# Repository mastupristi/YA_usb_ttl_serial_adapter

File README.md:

# USB-TTL Adapter with Auto Voltage Sensing

This is a simple open hardware project for a USB-to-TTL serial adapter based on the FTDI FT232RNL chip. The main feature of this adapter is its automatic voltage level detection, supporting TTL I/O levels from 1.8V to 5V without requiring manual jumper selection.

## Motivation

There are many USB-to-TTL adapters available on the market, such as:

- [AZDelivery FT232RL Adapter](https://www.amazon.it/AZDelivery-FT232RL-Adattatore-convertitore-Gratuito/dp/B01N9RZK6I)
- [DSD TECH SH-U09C2 Adapter](https://www.amazon.it/DSD-TECH-SH-U09C2-Adattatore-Programmazione/dp/B07TXVRQ7V/)

However, most of them require the user to manually set the voltage level using jumpers or switches. This can be inconvenient or even risky if the user forgets to set, or does not know exactly the correct voltage, potentially damaging the target device.

## Key Features

- Based on **FTDI FT232RNL** USB-serial bridge.
- Supports **1.8V to 5V TTL I/O levels**.
- **No jumpers or switches** required to select voltage.
- Uses **TI TXU0202** dual-channel voltage level translator for automatic level adaptation.
- Only **RX** and **TX** signals are used (no RTS/CTS or other control signals).
- Two mirrored TTL connectors with **inverted RX/TX** pinout for flexible wiring
- All schematic symbols and footprints have fields populated for **automated assembly on [JLCPCB](https://jlcpcb.com/)**

## Auto Voltage Detection

This adapter eliminates the need for manual voltage configuration. Thanks to the TXU0202 level shifter, the adapter automatically adapts to the voltage of the connected target device. This makes it safer and easier to use, especially when working with multiple devices operating at different logic levels.

## TTL Pinout

The board provides **two 1x4 pin headers** on the TTL side, with the same signals but **mirrored RX/TX orientation**. This simplifies usage with different target pinouts.

### Pinout (both connectors):

```
[ VCC_TTL | TX | RX | GND ]  ← Connector A
[ VCC_TTL | RX | TX | GND ]  ← Connector B (mirrored)
```

This layout helps avoid the common issue of crossed RX/TX lines between the adapter and the target device.

There are indications in the silkscreen to identify the VCC_TTL and GND pins.

## Manufacturing Support

This project includes files suitable for production with **[JLCPCB](https://jlcpcb.com/)**:

- [usb_uart_1V8_bom_top.csv](usb_uart_1V8_bom_top.csv) and [usb_uart_1V8_bom_bot.csv](usb_uart_1V8_bom_bot.csv): Bill of materials, with fields compatible with JLCPCB's parts selection tool (only **top** side populated)
- [usb_uart_1V8_cpl_top.csv](usb_uart_1V8_cpl_top.csv) and [usb_uart_1V8_cpl_bot.csv](usb_uart_1V8_cpl_bot.csv): Pick-and-place files (only **top** side contains components)
- All schematic symbols and footprints include **LCSC part numbers**, **JLC footprints** and assembly attributes

## Design Tools

This project was developed using **KiCad 9.0.1**.

## Repository Contents

- KiCad design files are on he root dir of the repo
- `usb_uart_1V8.pretty/`: local footprint library
- `gerber/`: Production-ready Gerber + drill files, packed in [grb_usb_uart_1V8.zip](gerber/grb_usb_uart_1V8.zip)

## Rendering

Here is a rendering of the board

## License

This project is licensed under the **CERN-OHL-S v2** open hardware license.
See [LICENSE.CERN-OHL-S_v2.txt](LICENSE) for more information.

## How to Contribute

Feel free to open issues or submit pull requests if you find bugs or want to suggest improvements.

## Acknowledgments

This project was inspired by the analysis in this blog post:
[https://www.electrothinks.com/2024/02/ft232rl-usb-to-serial-uart-module.html](https://www.electrothinks.com/2024/02/ft232rl-usb-to-serial-uart-module.html)

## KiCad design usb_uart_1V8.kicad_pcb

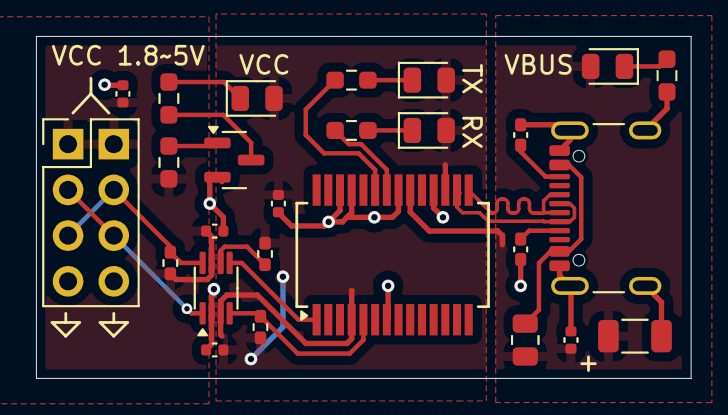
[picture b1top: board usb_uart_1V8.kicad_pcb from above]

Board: 2 copper layers, 36.4 x 19.0 mm, 26 parts (0 on the bottom side), 22 nets.

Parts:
C1, C3, C4, C5, C6: 100nF; C_0402_1005Metric
C2: 10uF; C_1206_3216Metric
D1, D2, D3, D4: NCD0805R1; LED_0805_2012Metric
FB1: GZ2012D601TF; R_0805_2012Metric
J1: USB_C_Receptacle_USB2.0_16P; USB_C_Receptacle_GCT_USB4105-xx-A_16P_TopMnt_Horizontal
J2: Conn_02x04_Odd_Even; PinHeader_2x04_P2.54mm_Vertical
Q1: MMBT3904; SOT-23
R1: 1k5; R_0603_1608Metric_Pad0.98x0.95mm_HandSolder
R2, R3: 270; R_0603_1608Metric_Pad0.98x0.95mm_HandSolder
R4, R5, R6: 10k; R_0402_1005Metric_Pad0.72x0.64mm_HandSolder
R7: 470; R_0603_1608Metric_Pad0.98x0.95mm_HandSolder
R8: 47k; R_0603_1608Metric_Pad0.98x0.95mm_HandSolder
R9, R10: 5k1; C_0402_1005Metric_Pad0.74x0.62mm_HandSolder
U1: FT232RNL; SSOP-28_5.3x10.2mm_P0.65mm
U2: TXU0202DCU; VSSOP-8_2.3x2mm_P0.5mm

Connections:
+3V3: C3.1, C4.1, D2.2 (A), D3.2 (A), D4.2 (A), R4.1, R5.1, U1.4 (VCCIO), U1.17 (3V3OUT), U2.3 (VCCA)
/D+: J1.A6 (D+), J1.B6 (D+), U1.15 (USBD+)
/D-: J1.A7 (D-), J1.B7 (D-), U1.16 (USBD-)
/RX: J2.3, J2.6, U2.1 (B2)
/RXL: R3.2, U1.22 (CBUS1)
/RX_3V3: R4.2, U1.5 (RXD), U2.4 (A2Y)
/TX: J2.4, J2.5, R6.2, U2.8 (B1Y)
/TXL: R2.2, U1.23 (CBUS0)
/TX_3V3: U1.1 (TXD), U2.5 (A1)
GND: C1.2, C2.2, C3.2, C4.2, C5.2, C6.2, J1.A1 (GND), J1.A12 (GND), J1.B1 (GND), J1.B12 (GND), J1.S1 (SHIELD), J2.7, J2.8, Q1.2 (E), R1.2, R9.2, R10.2, U1.7 (GND), U1.18 (GND), U1.21 (GND), U1.25 (AGND), U1.26 (TEST), U2.2 (GND)
unnamed: D1.1 (K), R1.1
unnamed: D2.1 (K), R2.1
unnamed: D3.1 (K), R3.1
unnamed: D4.1 (K), R7.1
unnamed: FB1.1, J1.A4 (VBUS), J1.A9 (VBUS), J1.B4 (VBUS), J1.B9 (VBUS)
unnamed: J1.A5 (CC1), R9.1
unnamed: J1.B5 (CC2), R10.1
unnamed: Q1.1 (B), R8.1
unnamed: Q1.3 (C), R7.2
unnamed: R5.2, U2.6 (OE)
VBUS: C1.1, C2.1, D1.2 (A), FB1.2, U1.20 (VCC)
VCC_TTL: C5.1, C6.1, J2.1, J2.2, R6.1, R8.2, U2.7 (VCCB)

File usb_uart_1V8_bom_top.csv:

"Comment","Designator","Footprint","LCSC Part #"
"100nF","C1 C3 C4 C5 C6","0402","C1525"
"10uF","C2","CASE-A-3216-18(mm)","C7171"
"NCD0805R1","D1 D2 D3 D4","0805","C84256"
"GZ2012D601TF","FB1","0805","C1017"
"USB_B_Micro","J1","SMD","C132563"
"Conn_02x04_Odd_Even","J2","",""
"MMBT3904","Q1","SOT-23","C20526"
"1k5","R1","0603","C22843"
"270","R2 R3","0603","C22966"
"10k","R4 R5 R6","0402","C25744"
"470","R7","0603","C23179"
"47k","R8","0603","C25819"
"FT232RNL","U1","SSOP-28","C5246810"
"TXU0202DCU","U2","VSSOP-8","C5186957"

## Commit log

2025-03-29 [ADD] first import
2025-03-30 [UPG] ft232 supplied by 5V3 and added level shifter
2025-03-30 [UPG] pcb
2025-03-30 [UPG] almost finished PCB
2025-03-31 [UPG] level shifter: 2 become 1
2025-04-08 [CLN] a little cleanup
2025-04-08 [UPG] production files
2025-04-08 [CLN] cleanup
2025-04-12 [UPG] ver 0.4
    - changed some values
    - PN basic from JLCPCB
    - reduced dimension
    - changed some components, now are bigger, eg. 0402 -> 0603
    - used handsolder footprint for fome resistor
    - changed led (less efficient)
2025-04-24 [UPG] .gitignore
2025-04-24 [UPG] changed connector from micro-b to usb-c
